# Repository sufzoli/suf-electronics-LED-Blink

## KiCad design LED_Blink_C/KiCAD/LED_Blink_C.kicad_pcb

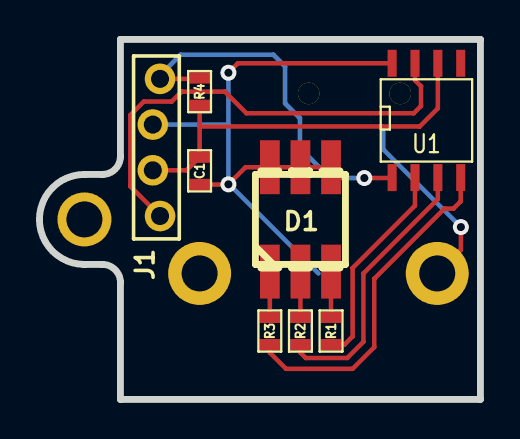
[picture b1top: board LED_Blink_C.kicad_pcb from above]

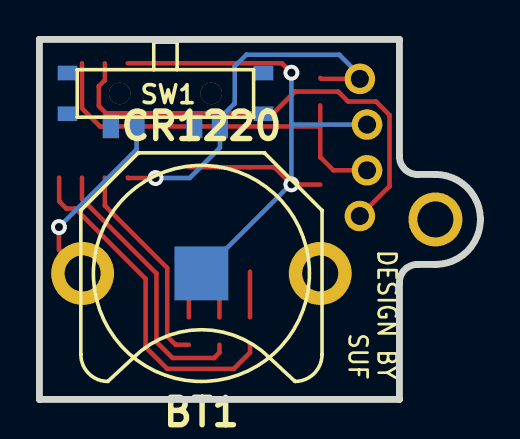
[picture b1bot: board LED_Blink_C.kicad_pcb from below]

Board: 2 copper layers, 24.5 x 20.0 mm, 11 parts (2 on the bottom side), 11 nets.

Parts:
BT1: CR1220; Keystone-3001
C1: 1nF; SM0603
D1: OF-SMD5060RGB; PLCC-6
J1: SBW; HDR-TI-SBW
MNT_HOLE_2: Val**; MNT_HOLE_2
R1, R2, R3: 470; SM0603
R4: 47K; SM0603
SW1: MLL1300S
U1: MSP430G2230; SOIC-8

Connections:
GND: BT1.2, C1.2, D1.4, D1.5, D1.6, J1.3, U1.8
unnamed: BT1.1, SW1.3
unnamed: J1.1, U1.7
unnamed: C1.1, J1.2, R4.2, U1.6
unnamed: D1.3, R1.1
unnamed: D1.2, R2.1
unnamed: D1.1, R3.1
unnamed: R3.2, U1.4
unnamed: R2.2, U1.3
unnamed: R1.2, U1.2
VCC: J1.4, R4.1, SW1.1, U1.1

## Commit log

2014-01-23 Finalized Gerber files for manufacturing
2021-03-20 Add MSP430 based code
